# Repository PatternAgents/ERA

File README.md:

# ERA Embedded Rack Architecture 

This repository contains Open Source Hardware Reference Designs for the Embedded Rack Architecture (ERA),
a new design pattern for the interconnection and packaging of Modular Audio/Video equipment.

The Embedded Rack Architecture (ERA) is a new, 
Open Source Hardware (OSHW) specification for 
Modular Audio/Video equipment that is being co-developed by a number of
cooperating companies and individuals in the audio field,
and is backward compatible with the Eurorack specification (aka Legacy Eurorack). 

For more information, please see the [ERA Wiki](https://github.com/patternagents/ERA/wiki)!

If you'd like to be involved in the development of the new 
Embedded Rack Architecture (ERA) specifications and reference designs,
then please contact us at :  [PatternAgents](https://patternagents.com/store)

-----------------------------------------------------

Eurorack (Legacy) References and Articles

[Doepfer- Eurorack ](http://www.doepfer.de/a100_man/a100m_e.htm)

[Wikipedia-Doepfer](https://en.wikipedia.org/wiki/Doepfer_A-100)

[SDIY Info](https://www.sdiy.info/w/Eurorack)

-----------------------------------------------------

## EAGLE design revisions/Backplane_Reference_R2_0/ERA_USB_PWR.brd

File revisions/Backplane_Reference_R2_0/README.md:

## ERA ##

Embedded Rack Architecture 2.0 Specifications and Reference Designs 

-----------------------------------------------------

This repository contains Open Source Hardware Reference Designs for ERA 2.0

-----------------------------------------------------

The Backplane Reference is a simple, passive, fourteen (14) slot Backplane in a compact form factor.
The Embedded Rack Architecture supports the following signals:

* Ground (GND)        (4 pins)
* +12V DC (1A min)    (2 pins)
* -12V DC (.5A min)   (2 pins)
* +5V DC (1A min)     (2 pins)
* Control Voltage In  (1 pin)   (-5.0 to 5.0 volts)
* Control Voltage Out (1 pin)   (-5.0 to 5.0 volts)
* Gate In             (1 pin)   (0.0 - 5.0 volts)
* Gate Out            (1 pin)   (0.0 - 5.0 volts)
* I2C SDA             (1 pin)   (0.0 - 5.0 volts)
* I2C SCL             (1 pin)   (0.0 - 5.0 volts)

Because a reverse polarity power connection can short the SDA & SCL pins to the +12V DC pins,
the ERA specification includes a simple N-Channel Mosfet circuit that provides both Level Shifting 
(for lower voltage CPU interfaces) and over-voltage/reverse-voltage protection on the ERA I2C Signals (SDA & SCL). 
The circuit is described in the ERA Module Reference Design.

-----------------------------------------------------
For more information, please see the [ERA Wiki](https://github.com/patternagents/ERA/wiki)!
-----------------------------------------------------

-----------------------------------------------------

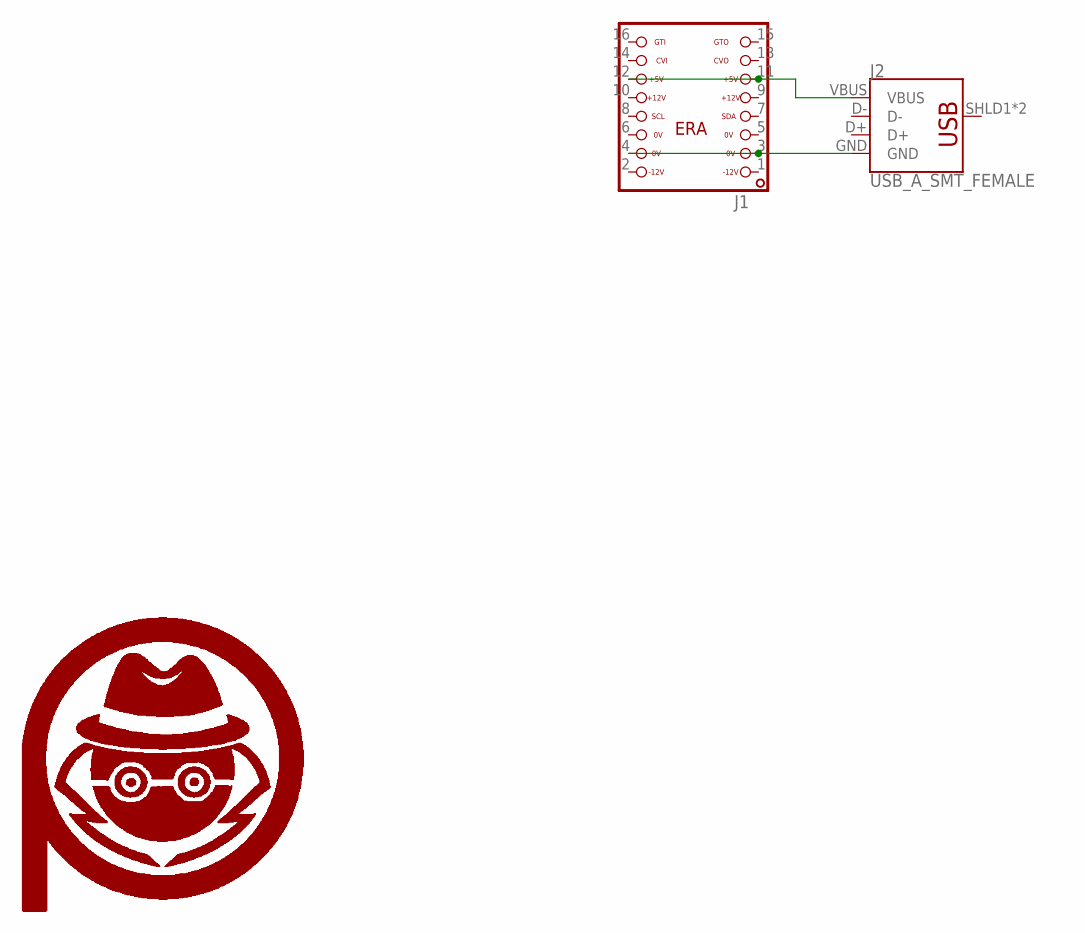
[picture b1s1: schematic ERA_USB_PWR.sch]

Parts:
J1: ERA_16PIN-NOSILK; ERA-16-NOSILK
J2: USB_A_SMT_FEMALE; USB-A-S-SILK-FEMALE
U$1, U$2: PA_LOGO_SYMSMALL; PA_LOGO_AGENT_SMALL_SYM

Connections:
GND: J1.3, J1.4, J2.GND
unnamed: J1.11, J1.12, J2.VBUS

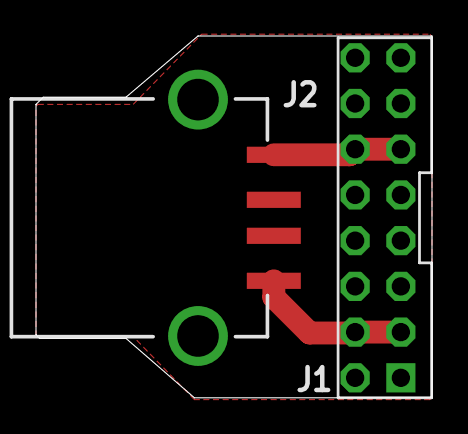
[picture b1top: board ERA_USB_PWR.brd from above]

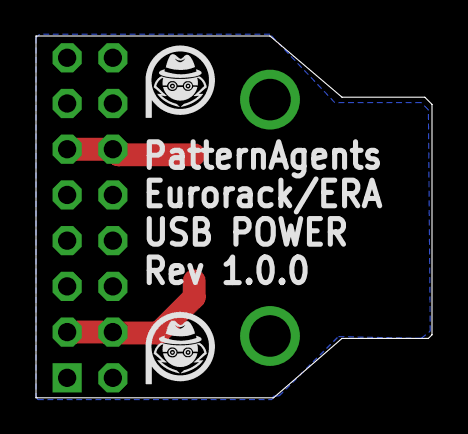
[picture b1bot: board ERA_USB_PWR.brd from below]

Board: 2 copper layers, 22.0 x 20.1 mm, 4 parts (2 on the bottom side), 2 nets.

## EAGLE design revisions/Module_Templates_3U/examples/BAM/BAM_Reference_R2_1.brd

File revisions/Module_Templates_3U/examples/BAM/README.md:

# Bus Access Module (BAM)

Bus Access Module - ERA Reference Design

Format : ERA / Eurorack 

Height : 3U 

Width: 3HP

Depth : 1.0 cm

Power : +12V 40mA, -12V 40mA

Jacks : 3.5mm mono

The Bus Access Module (BAM) is used as a passive break out board for 
ERA backplane signals to the patchbay/front panel.
It includes a legacy Eurorack Connector as well as an ERA connector
for compatibility with other/older backplanes and modules.
A buffered, dual color LED is used as an optional CV/Gate activity indicator. 

-----------------------------------------------------

-----------------------------------------------------

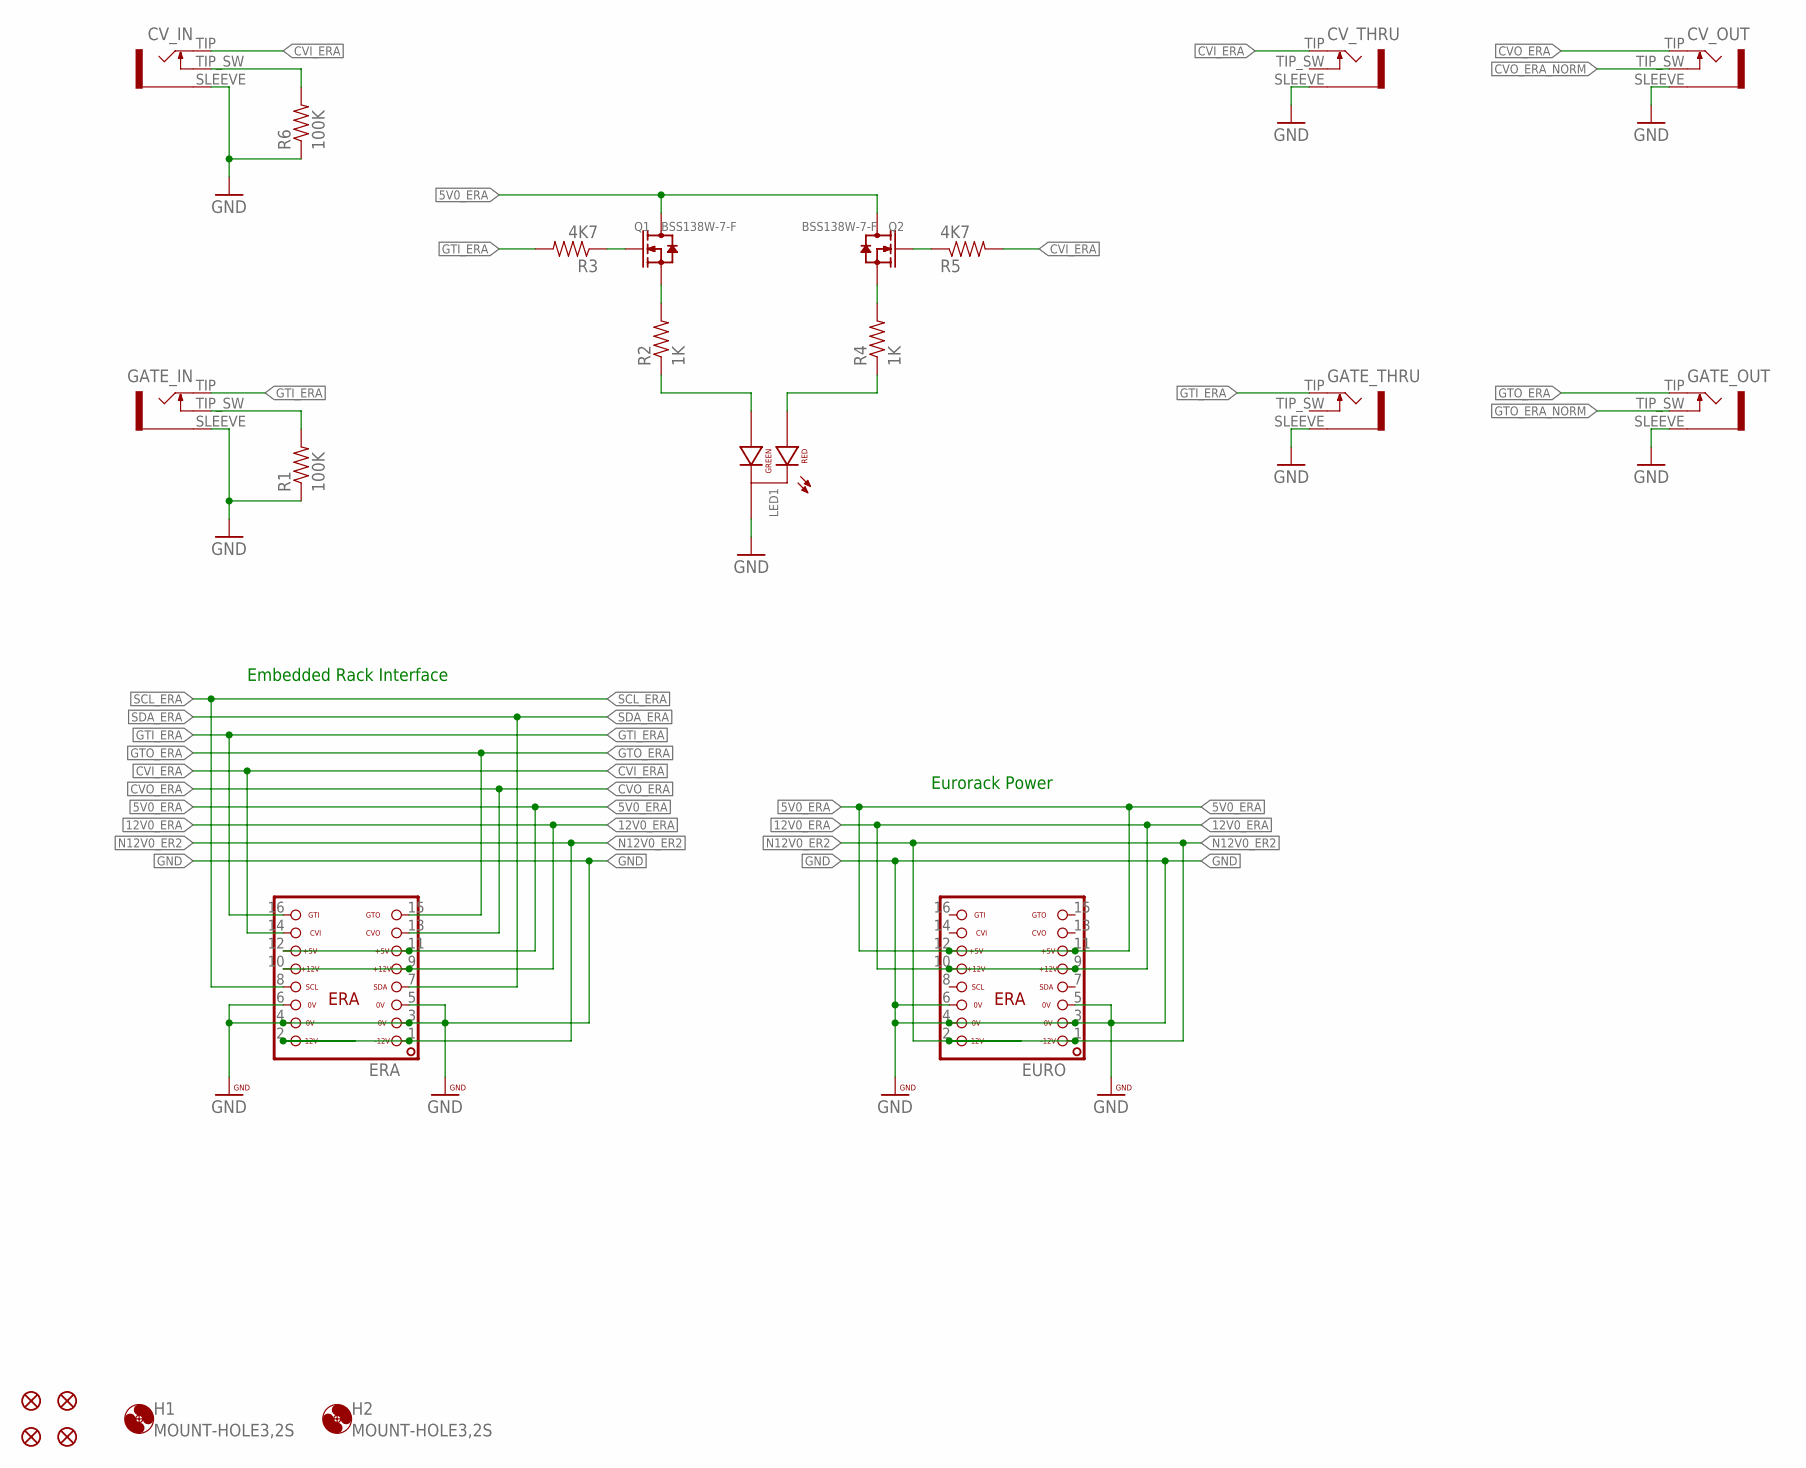
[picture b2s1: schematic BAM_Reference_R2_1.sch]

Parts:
CV_IN: JACK-3_5MM-MONO-SW-MJ_3502; MJ-3502
CV_OUT: JACK-3_5MM-MONO-SW-MJ_3502; MJ-3502
CV_THRU: JACK-3_5MM-MONO-SW-MJ_3502; MJ-3502
ERA: ERA-SHROUD; ERA
EURO: ERA-SHROUD; ERA
FID1, FID2, FID3, FID4: FIDUCIALUFIDUCIAL; MICRO-FIDUCIAL
GATE_IN: JACK-3_5MM-MONO-SW-MJ_3502; MJ-3502
GATE_OUT: JACK-3_5MM-MONO-SW-MJ_3502; MJ-3502
GATE_THRU: JACK-3_5MM-MONO-SW-MJ_3502; MJ-3502
H1, H2: MOUNT-HOLE3,2S; 3,2,SMALL
LED1: LED-RG-CC-PTH-G18500; LED-RG-PANEL
Q1, Q2: BSS138W-7-F; SOT-23
R1, R6: 100K; 0603-RES
R2, R4: 1K; 0603-RES
R3, R5: 4K7; 0603-RES

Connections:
5V0_ERA: ERA.11, ERA.12, EURO.11, EURO.12, Q1.3 (D), Q2.3 (D)
12V0_ERA: ERA.9, ERA.10, EURO.9, EURO.10
CVI_ERA: CV_IN.TIP, CV_THRU.TIP, ERA.14, R5.2
CVO_ERA: CV_OUT.TIP, ERA.13
CVO_ERA_NORM: CV_OUT.TIP_SW
GND: CV_IN.SLEEVE, CV_OUT.SLEEVE, CV_THRU.SLEEVE, ERA.3, ERA.4, ERA.5, ERA.6, EURO.3, EURO.4, EURO.5, EURO.6, GATE_IN.SLEEVE, GATE_OUT.SLEEVE, GATE_THRU.SLEEVE, LED1.CC (CATHODE), R1.1, R6.1
GTI_ERA: ERA.16, GATE_IN.TIP, GATE_THRU.TIP, R3.2
GTO_ERA: ERA.15, GATE_OUT.TIP
GTO_ERA_NORM: GATE_OUT.TIP_SW
N12V0_ER2: ERA.1, ERA.2, EURO.1, EURO.2
unnamed: LED1.GREEN (GREEN_CATHODE), R2.1
unnamed: LED1.RED (RED_CATHODE), R4.1
unnamed: Q1.1 (G), R3.1
unnamed: Q2.2 (S), R4.2
unnamed: Q2.1 (G), R5.1
unnamed: Q1.2 (S), R2.2
unnamed: CV_IN.TIP_SW, R6.2
unnamed: GATE_IN.TIP_SW, R1.2
SCL_ERA: ERA.8
SDA_ERA: ERA.7

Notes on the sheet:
Embedded Rack Interface
Eurorack Power

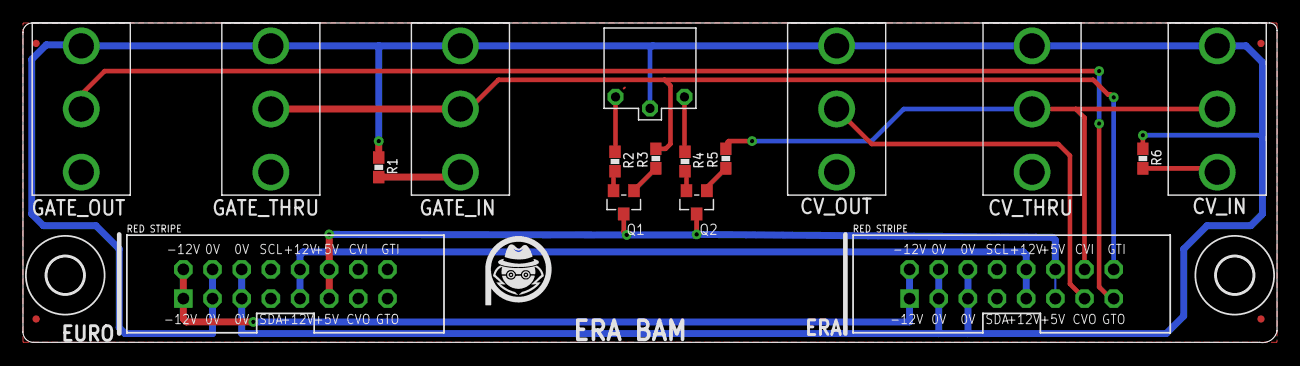
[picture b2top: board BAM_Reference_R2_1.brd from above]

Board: 2 copper layers, 109.2 x 27.8 mm, 26 parts (1 on the bottom side), 16 nets.

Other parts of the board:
U$1, U$2: PA_LOGO_SYMMED; PA_LOGO_AGENT_MED_SYM
U$48: BY_CC_SA_TEXTTEXT; BY_CC_SA_TEXT

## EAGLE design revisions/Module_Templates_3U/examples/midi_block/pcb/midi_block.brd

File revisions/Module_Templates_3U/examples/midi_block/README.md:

# midi_block

Format : ERA / Eurorack

Height : 3U 

Width: 6HP

Depth : 1.0 cm

Power : +5V 35mA

Jacks : DIN 5-PIN

-----------------------------------------------------
This repository contains Open Source Hardware Reference Designs for Embedded Rack Architecture (ERA)
that anyone can use or fabricate for themselves.

For more information, please see the [ERA Wiki](https://github.com/halcyonmodular/ERA/wiki)!

Embedded Rack Architecture (ERA) is a new, Open Source Hardware (OSHW) specification for 
Modular Audio/Video equipment that is being co-developed by a number of
cooperating companies and individuals in the audio field,
and is completely backward compatible with Eurorack (Legacy). 

-----------------------------------------------------

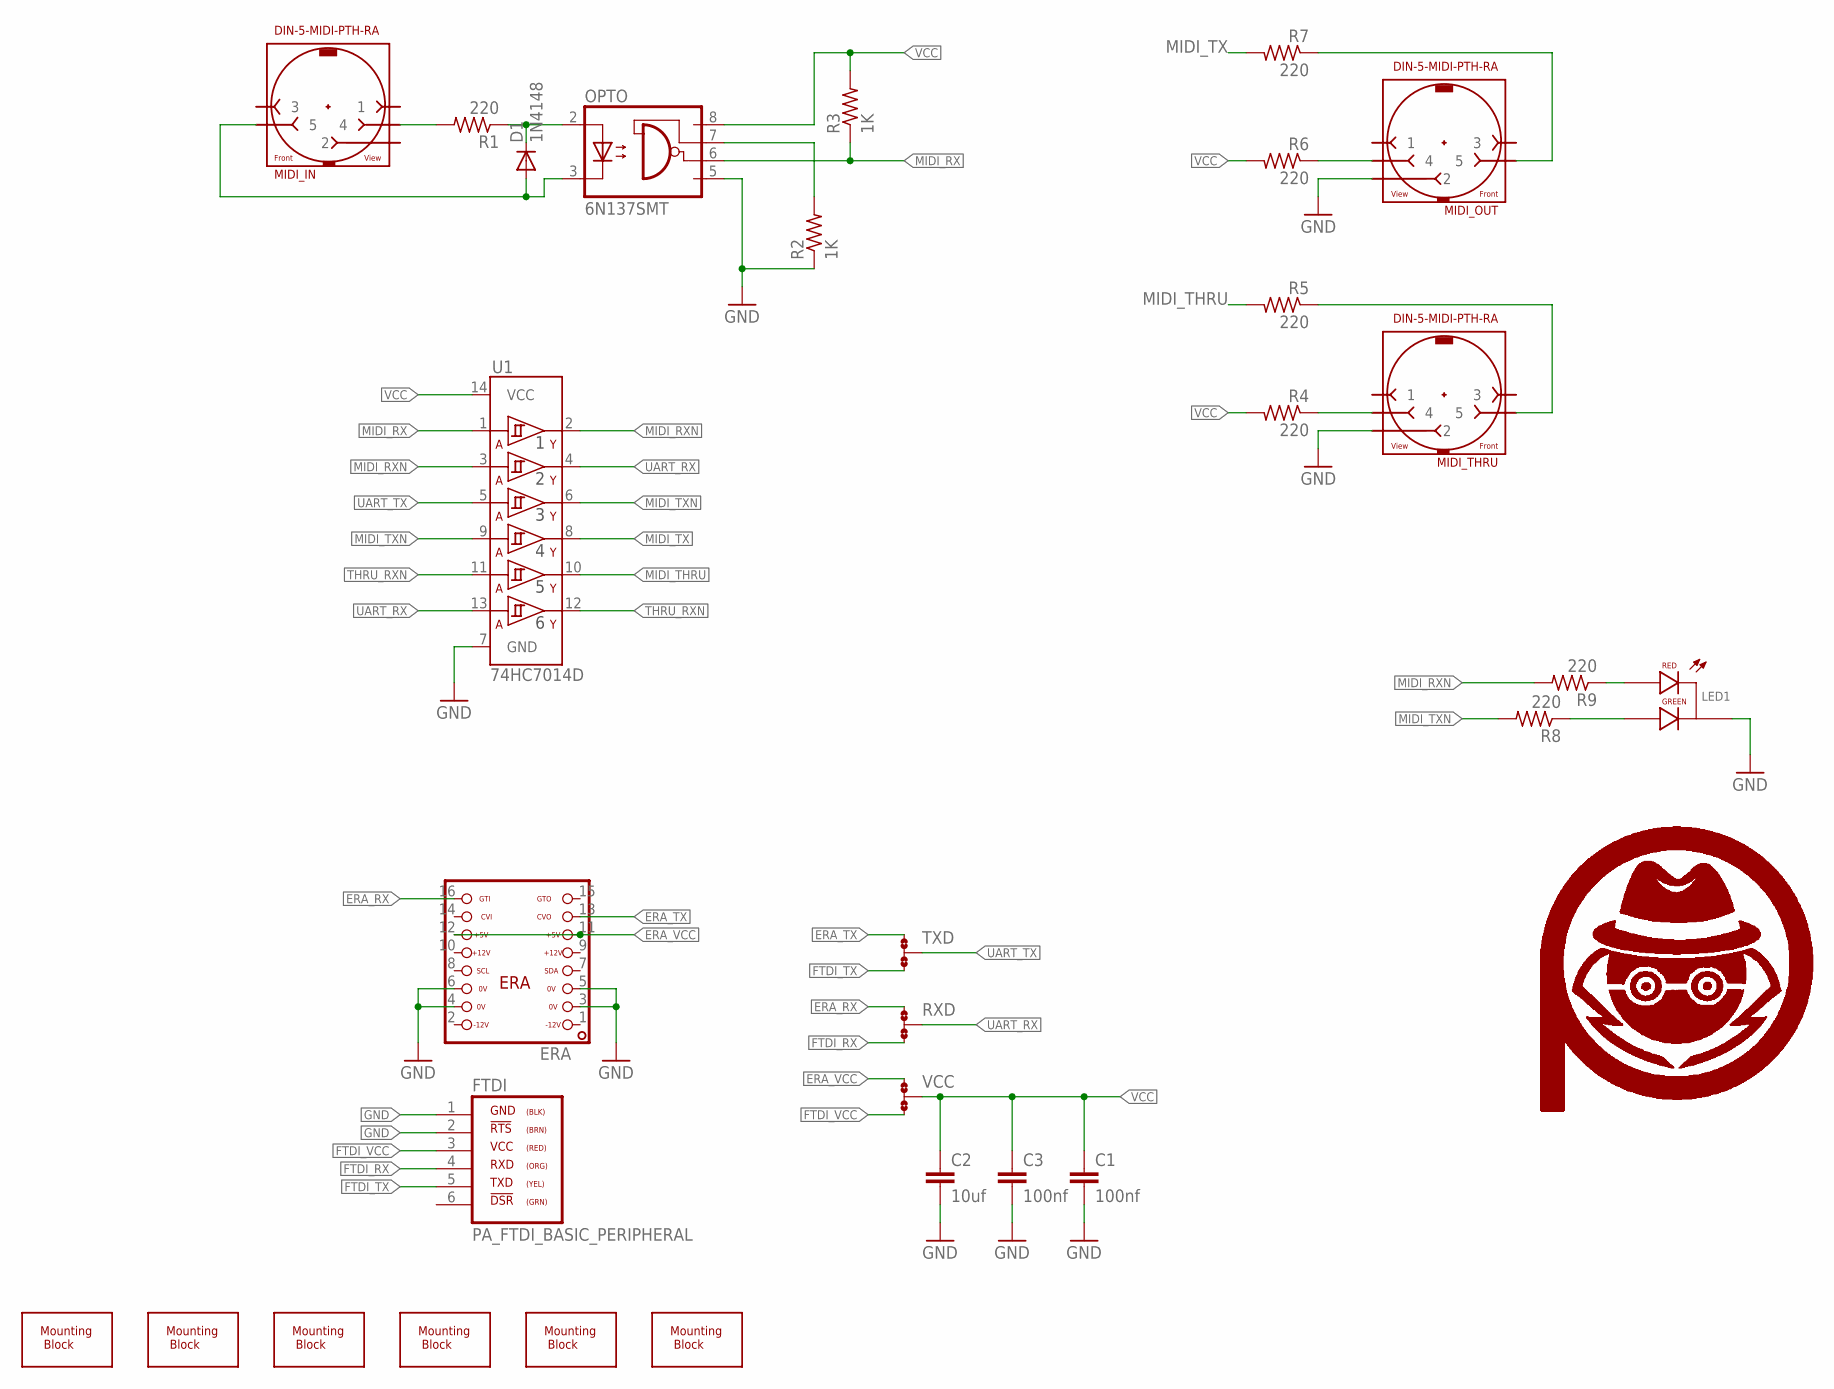
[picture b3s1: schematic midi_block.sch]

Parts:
C1, C3: 100nf; 0603-CAP
C2: 10uf; 0603-CAP
D1: 1N4148; SOD323-W
ERA: ERA-SHROUD; ERA
FTDI: PA_FTDI_BASIC_PERIPHERAL; PA_PMOD_SIL_MALE
LED1: LED-RG-CC-PTH-G18500; LED-RG-PANEL
MIDI_IN: DIN-5-MIDI-PTH-RA; DIN-5-PTH-RA-SUPPORT
MIDI_OUT: DIN-5-MIDI-PTH-RA; DIN-5-PTH-RA-SUPPORT
MIDI_THRU: DIN-5-MIDI-PTH-RA; DIN-5-PTH-RA-SUPPORT
OPTO: 6N137SMT; DIL8-SMD
R1, R4, R5, R6, R7, R8, R9: 220; R0603
R2, R3: 1K; R0603
RXD: JMP-3-NO-PTH; JMP-3-NO-PTH-2.54
TXD: JMP-3-NO-PTH; JMP-3-NO-PTH-2.54
U1: 74HC7014D; SOIC-14
U$1, U$2, U$3, U$4, U$7, U$8: PCB-MB-SIDE; PCB-MB-01-SIDE
U$5, U$6: PA_LOGO_SYMMED; PA_LOGO_AGENT_MED_SYM
VCC: JMP-3-NO-PTH; JMP-3-NO-PTH-2.54

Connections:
CL_IN: MIDI_IN.4, R1.2
ERA_RX: ERA.16, RXD.1
ERA_TX: ERA.13, TXD.1
ERA_VCC: ERA.11, ERA.12, VCC.1
FTDI_RX: FTDI.4, RXD.3
FTDI_TX: FTDI.5, TXD.3
FTDI_VCC: FTDI.3, VCC.3
GND: C1.2, C2.2, C3.2, ERA.3, ERA.4, ERA.5, ERA.6, FTDI.1, FTDI.2, LED1.CC (CATHODE), MIDI_OUT.2, MIDI_THRU.2, OPTO.5 (GND), R2.1, U1.7 (GND)
MIDI_IN: D1.A, MIDI_IN.5, OPTO.3 (C)
MIDI_OUT: MIDI_OUT.5, R7.1
MIDI_OUT1: MIDI_THRU.5, R5.1
MIDI_RX: OPTO.6 (VO), R3.1, U1.1 (1A)
MIDI_RXN: R9.2, U1.2 (1Y), U1.3 (2A)
MIDI_THRU: R5.2, U1.10 (5Y)
MIDI_TX: R7.2, U1.8 (4Y)
MIDI_TXN: R8.2, U1.6 (3Y), U1.9 (4A)
unnamed: LED1.RED (RED_CATHODE), R9.1
unnamed: LED1.GREEN (GREEN_CATHODE), R8.1
unnamed: MIDI_THRU.4, R4.1
unnamed: OPTO.7 (VE), R2.2
unnamed: D1.C, OPTO.2 (A), R1.1
unnamed: MIDI_OUT.4, R6.1
THRU_RXN: U1.11 (5A), U1.12 (6Y)
UART_RX: RXD.2, U1.4 (2Y), U1.13 (6A)
UART_TX: TXD.2, U1.5 (3A)
VCC: C1.1, C2.1, C3.1, OPTO.8 (VCC), R3.2, R4.2, R6.2, U1.14 (VCC), VCC.2

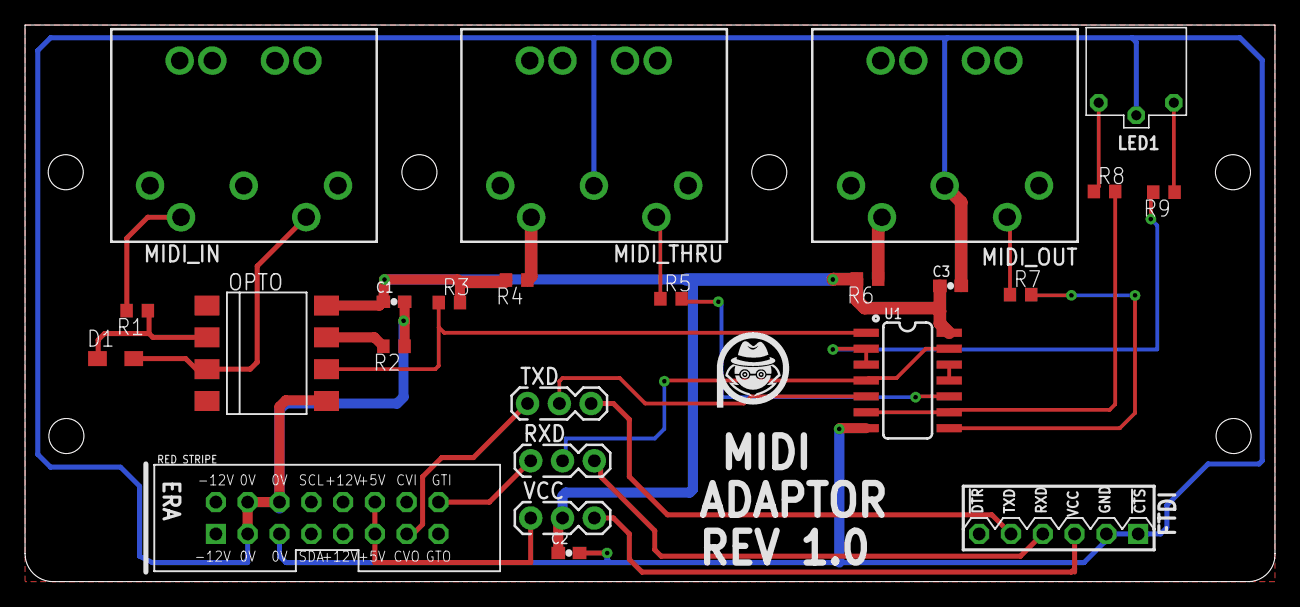
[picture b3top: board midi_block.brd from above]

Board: 2 copper layers, 99.8 x 44.5 mm, 32 parts (1 on the bottom side), 26 nets.

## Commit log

2018-01-19 initial version
2018-01-20 Update Backplane Reference
2018-01-20 update backplane images
2018-04-10 4/10 update
2020-07-01 Enlarge SwitchMult Front panel holes for easier assembly/operation

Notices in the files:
README.md:
License: CC BY 4.0
parts and their libraries:
SparkFun-Connectors: Licensing: Creative Commons ShareAlike 4.0 International - https://creativecommons.org/licenses/by-sa/4.0
PatternAgents-Logos: License : http://creativecommons.org/licenses/by-sa/3.0
(Creative Commons 3.0)
PatternAgents-Logos: Source : http://wiki.creativecommons.org/CC_markers
